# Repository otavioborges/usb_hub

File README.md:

# Active USB Hub - Ello Govnor

This project comprises shcematics and PCB for a active USB Hub. Using a USB2514B for USB switching and a LPC11U35/401 for host and power control.

## Using the Project

Published under GNU v3 license. Project created on KiCAD v5.0.2. Using default software libraries

## Handbonning capabilities

The project includes three different types of handbonning. **USE WITH CAUTION**.

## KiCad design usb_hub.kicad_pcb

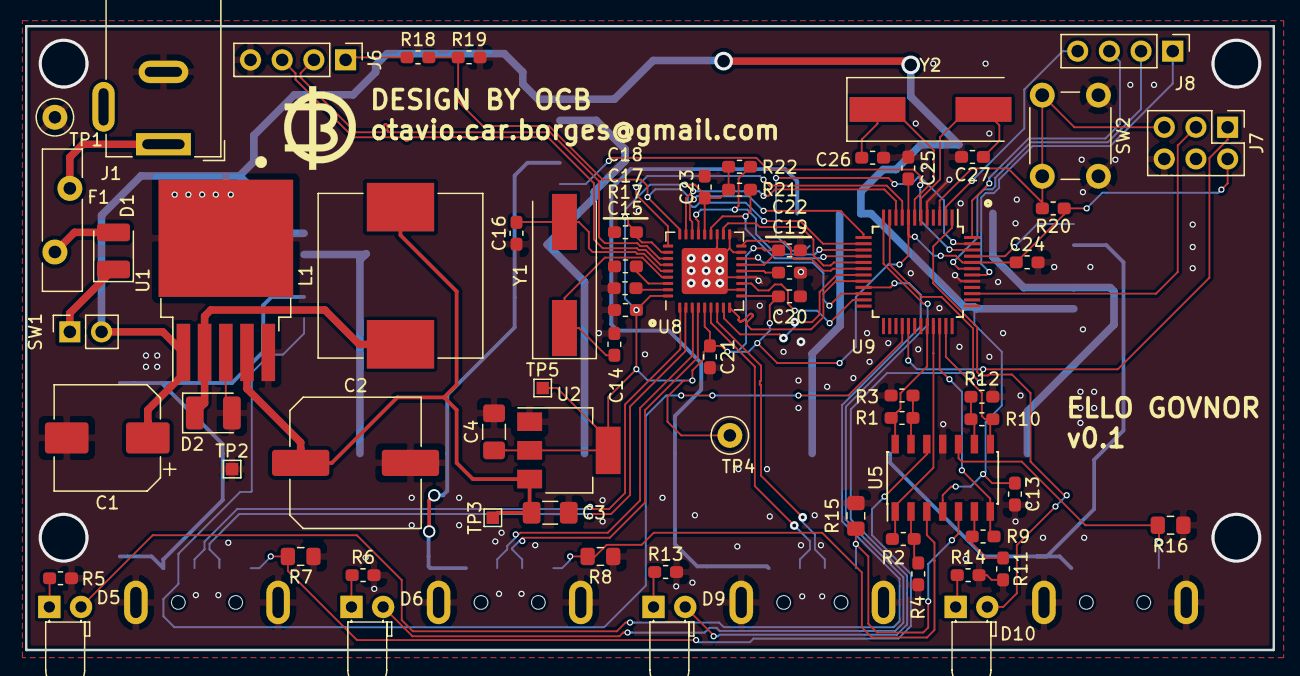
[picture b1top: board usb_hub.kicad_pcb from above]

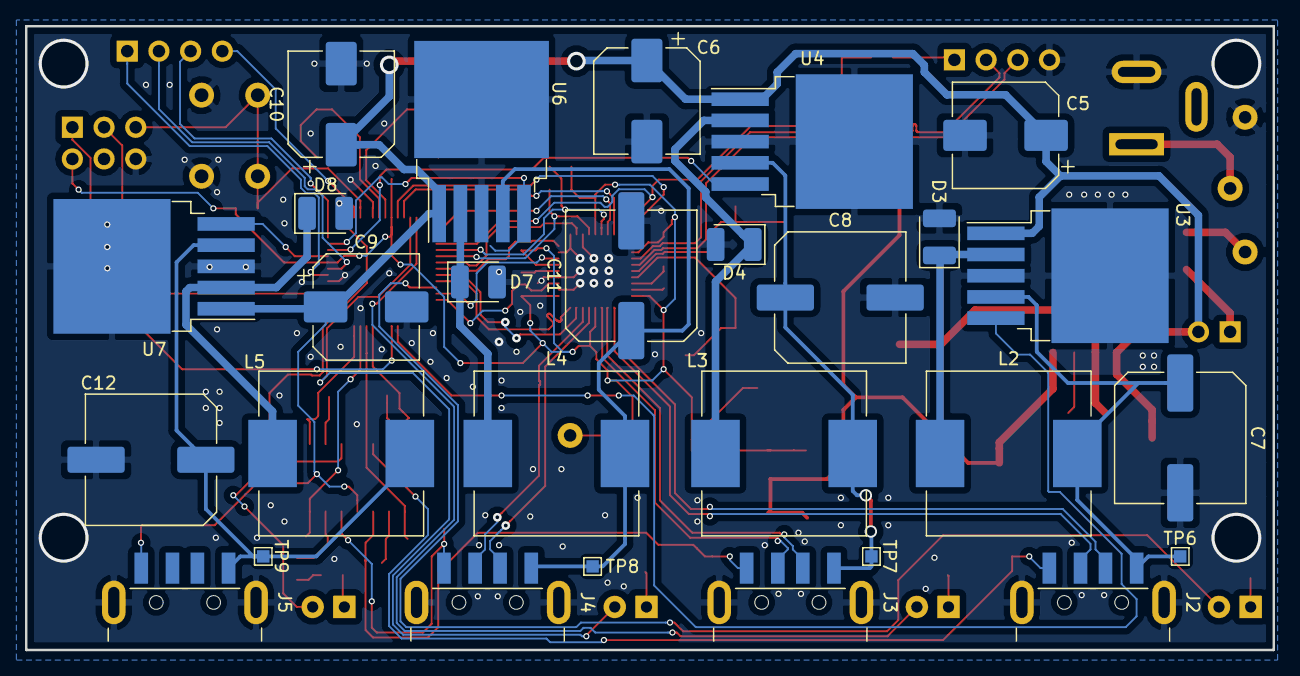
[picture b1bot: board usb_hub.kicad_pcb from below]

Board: 2 copper layers, 100.0 x 50.0 mm, 95 parts (28 on the bottom side), 75 nets.

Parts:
C1, C5, C6, C9, C10: 470uF; CP_Elec_8x10
C2, C7, C8, C11, C12: 220uF; C_Elec_10x10.2
C3, C4: 10uF; C_1206_3216Metric_Pad1.42x1.75mm_HandSolder
C13, C15, C17, C18, C19, C20, C21, C22, C23, C24, C25: 0.1uF; C_0603_1608Metric_Pad1.05x0.95mm_HandSolder
C14, C16, C26, C27: 39pF; C_0603_1608Metric_Pad1.05x0.95mm_HandSolder
D1, D2, D3, D4, D7, D8: VSSAF5L45; D_1210_3225Metric_Pad1.42x2.65mm_HandSolder
D5, D6, D9, D10: LED; LED_D3.0mm_Horizontal_O1.27mm_Z2.0mm
F1: 5A/16V; Fuse_Bourns_MF-RHT500
J1: Barrel_Jack_Switch; BarrelJack_Wuerth_6941xx301002
J2, J3, J4, J5: USB_A; USB_A_CNCTech_1001-011-01101_Horizontal
J6, J8: Conn_01x04; PinHeader_1x04_P2.54mm_Vertical
J7: Conn_02x03_Odd_Even; PinHeader_2x03_P2.54mm_Vertical
L1, L2, L3, L4, L5: 33uH; L_Neosid_SM-NE127_HandSoldering
R1, R2, R9, R10: 99k; R_0603_1608Metric_Pad1.05x0.95mm_HandSolder
R3, R4, R11, R12: 1k; R_0603_1608Metric_Pad1.05x0.95mm_HandSolder
R5, R6, R13, R14: 39; R_0603_1608Metric_Pad1.05x0.95mm_HandSolder
R7, R8, R15, R16: 10m; R_0805_2012Metric_Pad1.15x1.40mm_HandSolder
R17: 12K; R_0603_1608Metric_Pad1.05x0.95mm_HandSolder
R18: 5k; R_0603_1608Metric_Pad1.05x0.95mm_HandSolder
R19, R20, R21, R22: 10K; R_0603_1608Metric_Pad1.05x0.95mm_HandSolder
SW1: SW_DIP_x01; PinSocket_1x02_P2.54mm_Vertical
SW2: SW_Push; SW_PUSH_6mm
TP1, TP4: TestPoint_Alt; TestPoint_Loop_D1.80mm_Drill1.0mm_Beaded
TP2: TestPoint; TestPoint_Pad_1.0x1.0mm
TP3, TP5, TP6, TP7, TP8, TP9: Test_Point; TestPoint_Pad_1.0x1.0mm
U1, U3, U4, U6, U7: AP1501A-50K5G-13; TO-263-5_TabPin3
U2: LM1117-3.3; SOT-223-3_TabPin2
U5: LM324; SOIC-14_3.9x8.7mm_P1.27mm
U8: USB2514B_Bi; QFN-36-1EP_6x6mm_P0.5mm_EP3.7x3.7mm
U9: LPC11U35FBD48-401; TQFP-48_7x7mm_P0.5mm
Y1, Y2: 24MHz; Crystal_SMD_HC49-SD

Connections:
+3V3: C4.1, C15.1, C18.1, C20.1, C21.1, C22.1, C23.1, C24.1, C25.1, J7.2, R20.1, R21.1, R22.1, TP4.1, TP5.1, U2.2, U8.5, U8.10, U8.15, U8.23, U8.29, U8.36, U9.8, U9.44
+5V: C2.1, C3.1, L1.2, TP3.1, U1.4, U2.3
/FEED: F1.2, J1.1
/FUSED: D1.2, F1.1
/Host & Controller/HUB_HS: U8.25, U9.13
/Host & Controller/HUB_PWR1: U8.12, U9.23
/Host & Controller/HUB_PWR2: U8.16, U9.22
/Host & Controller/HUB_PWR3: U8.18, U9.18
/Host & Controller/HUB_PWR4: U8.20, U9.17
/Host & Controller/HUB_RESET: U8.26, U9.10
/Host & Controller/HUB_SUSP: U8.28, U9.9
/Host & Controller/MAIN_D+: J6.3, U8.31
/Host & Controller/MAIN_D-: J6.2, U8.30
/Host & Controller/MCU_SCL: R22.2, U8.24, U9.15
/Host & Controller/MCU_SDA: R21.2, U8.22, U9.16
/Host & Controller/MCU_VBUS_DET: R18.2, R19.1, U8.27, U9.14
/Host & Controller/RESET: J7.5, R20.2, SW2.2, U9.3
/Host & Controller/SPARE_1: J8.4, U9.2
/Host & Controller/SPARE_2: J8.3, U9.48
/Host & Controller/SPARE_3: J8.2, U9.43
/Host & Controller/SPARE_4: J8.1, U9.42
/Host & Controller/SWCLK: J7.1, U9.29
/Host & Controller/SWDIO: J7.3, U9.39
/SWITCH: D1.1, SW1.1
/USB Ports/USB1_5V: C7.1, J2.1, L2.2, TP6.1, U3.4
/USB Ports/USB2_5V: C8.1, J3.1, L3.2, TP7.1, U4.4
/USB Ports/USB3_5V: C11.1, J4.1, L4.2, TP8.1, U6.4
/USB Ports/USB4_5V: C12.1, J5.1, L5.2, TP9.1, U7.4
GND: C1.2, C2.2, C3.2, C4.2, C5.2, C6.2, C7.2, C8.2, C9.2, C10.2, C11.2, C12.2, C13.2, C14.2, C15.2, C16.2, C17.2, C18.2, C19.2, C20.2, C21.2, C22.2, C23.2, C24.2, C25.2, C26.2, C27.2, D2.2, D3.2, D4.2, D7.2, D8.2, J1.2, J2.5, J3.5, J4.5, J5.5, J6.4, J7.6, R3.2, R4.2, R5.2, R6.2, R7.1, R8.1, R11.2, R12.2, R13.2, R14.2, R15.1, R16.1, R17.2, R19.2, SW2.1, TP1.1, TP2.1, U1.3, U1.5, U2.1, U3.3, U4.3, U5.11, U6.3, U7.3, U8.11, U8.13, U8.17, U8.19, U8.21, U8.37, U9.5, U9.41
unnamed: C14.1, U8.33, Y1.1
unnamed: C16.1, U8.32, Y1.2
unnamed: C17.1, U8.34
unnamed: C19.1, U8.14
unnamed: C26.1, U9.7, Y2.1
unnamed: C27.1, U9.6, Y2.2
unnamed: D2.1, L1.1, U1.2
unnamed: D3.1, L2.1, U3.2
unnamed: D4.1, L3.1, U4.2
unnamed: D5.1, R5.1
unnamed: D6.1, R6.1
unnamed: D7.1, L4.1, U6.2
unnamed: D8.1, L5.1, U7.2
unnamed: D9.1, R13.1
unnamed: D10.1, R14.1
unnamed: J2.4, R7.2, U5.12
unnamed: J3.4, R8.2, U5.3
unnamed: J4.4, R15.2, U5.5
unnamed: J5.4, R16.2, U5.10
unnamed: J6.1, R18.1
unnamed: R1.2, R3.1, U5.13
unnamed: R2.2, R4.1, U5.2
unnamed: R10.2, R12.1, U5.9
unnamed: R9.2, R11.1, U5.6
unnamed: R17.1, U8.35
USB1_CHG: U3.5, U9.28
USB1_CUR: R1.1, U5.14, U9.32
USB1_D+: J2.3, U8.2
USB1_D-: J2.2, U8.1
USB1_ONLED: D5.2, U9.21
USB2_CHG: U4.5, U9.46
USB2_CUR: R2.1, U5.1, U9.33
USB2_D+: J3.3, U8.4
USB2_D-: J3.2, U8.3
USB2_ONLED: D6.2, U9.12
USB3_CHG: U6.5, U9.47
USB3_CUR: R9.1, U5.7, U9.34
USB3_D+: J4.3, U8.7
USB3_D-: J4.2, U8.6
USB3_ONLED: D9.2, U9.11
USB4_CHG: U7.5, U9.45
USB4_CUR: R10.1, U5.8, U9.35
USB4_ONLED: D10.2, U9.1
USB_MCU+: U8.9, U9.20
USB_MCU-: U8.8, U9.19
VBUS: C1.1, C5.1, C6.1, C9.1, C10.1, C13.1, SW1.2, U1.1, U3.1, U4.1, U5.4, U6.1, U7.1

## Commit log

2019-10-07 Initial project files commit. Ready for v0.1
2020-04-07 Fixing USB conn. gender and others: * 5V supply is simplified in one controller (55W); * Each USB port has it's on Current/Mode controller;
